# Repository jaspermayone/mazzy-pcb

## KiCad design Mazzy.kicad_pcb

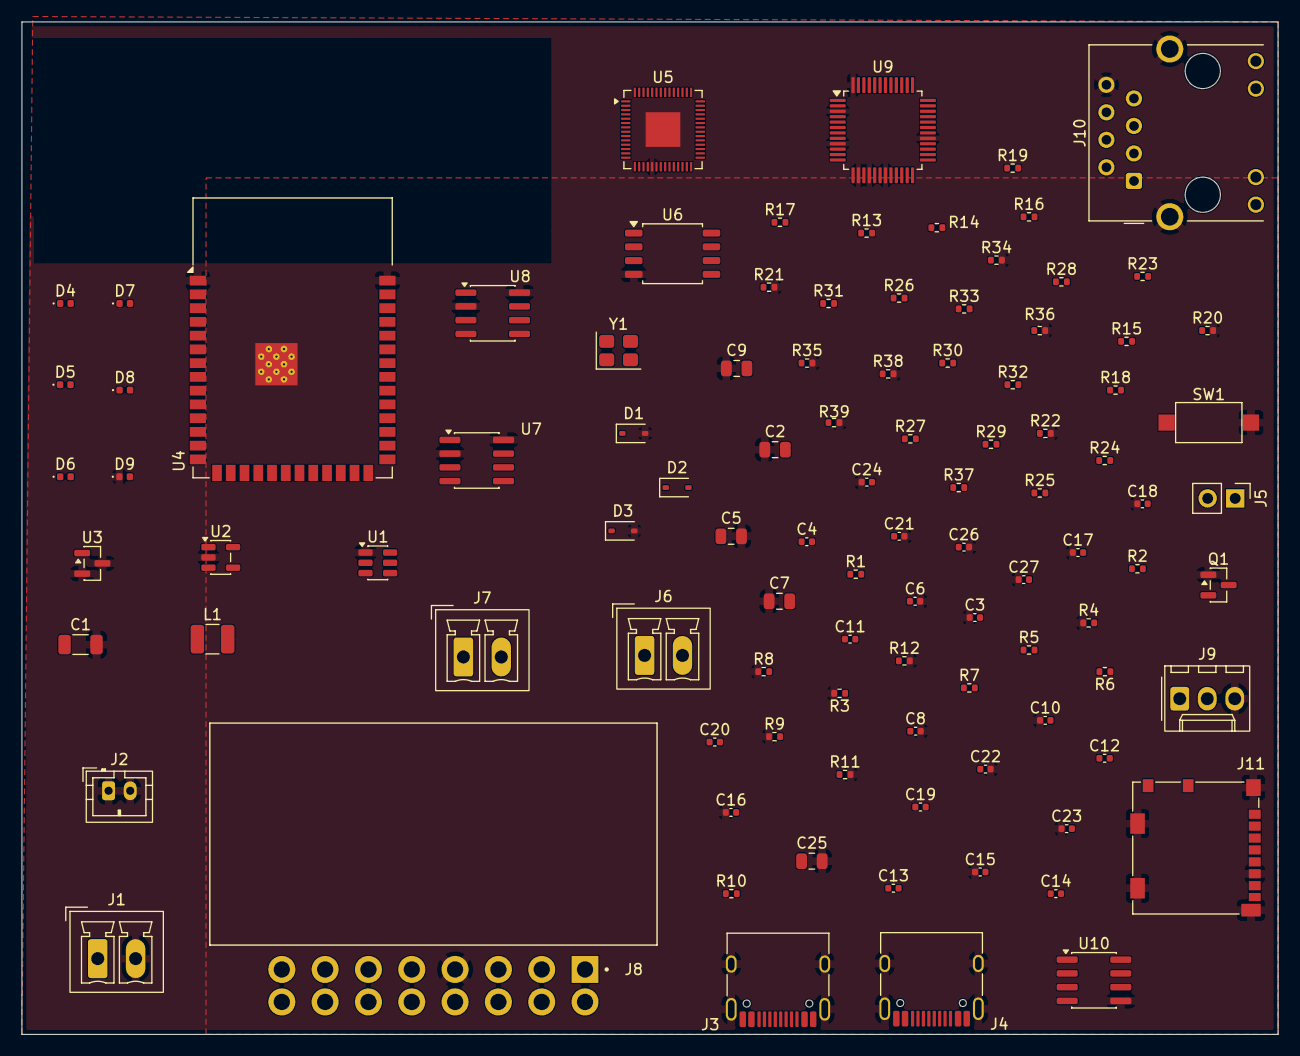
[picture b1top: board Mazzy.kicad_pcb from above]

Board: 2 copper layers, 116.0 x 93.5 mm, 100 parts (0 on the bottom side), 83 nets, no tracks yet.

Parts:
C1: 100uF; C_1206_3216Metric
C2, C9, C25: 10uF; C_0805_2012Metric
C3, C4, C6, C8, C10, C11, C12, C13, C14, C15, C16, C17, C18, C19, C20, C23, C24, C26, C27: 100nF; C_0402_1005Metric
C5: 22uF; C_0805_2012Metric
C7: 4.7uF; C_0805_2012Metric
C21, C22: 22pF; C_0402_1005Metric
D1: D_TVS; D_SOD-323
D2, D3: BAT54; D_SOD-323
D4, D5, D6, D7, D8, D9: LED; LED_0402_1005Metric
J1, J6, J7: Conn_01x02_Pin; PhoenixContact_MCV_1,5_2-G-3.5_1x02_P3.50mm_Vertical
J2: Conn_01x02_Pin; JST_PH_B2B-PH-K_1x02_P2.00mm_Vertical
J3, J4: USB_C_Receptacle_USB2.0_16P; USB_C_Receptacle_HRO_TYPE-C-31-M-12
J5: Conn_01x02_Pin; PinHeader_1x02_P2.54mm_Vertical
J8: OBD-II; COMTECH_C-OBD-II-16M
J9: SWC; Molex_KK-254_AE-6410-03A_1x03_P2.54mm_Vertical
J10: RJ45_Hanrun_HR911105A_Horizontal
J11: Micro_SD_Card_Det1; microSD_HC_Molex_104031-0811
L1: 10uH; L_1210_3225Metric
Q1: DMG2301L; SOT-23
R1, R2: 100k; R_0402_1005Metric
R3: 17.8k; R_0402_1005Metric
R4: 2k; R_0402_1005Metric
R5, R6, R7, R10, R26, R27, R28, R29, R30, R31, R32, R33: 10k; R_0402_1005Metric
R8, R9, R11, R12: 5.1k; R_0402_1005Metric
R13, R23: 49.9R; R_0402_1005Metric
R14, R15: 120R; R_0402_1005Metric
R16, R17, R18, R19, R21, R22: 330R; R_0402_1005Metric
R20: 12.4k; R_0402_1005Metric
R24, R25: 4.7k; R_0402_1005Metric
R34, R35, R36, R38, R39: 300R; R_0402_1005Metric
R37: 1k; R_0402_1005Metric
SW1: SW_Push; SW_SPST_CK_RS282G05A3
U1: TPS54302; SOT-23-6
U2: MCP73831-2-OT; SOT-23-5
U3: MCP100-300D; SOT-23
U4: ESP32-S3-WROOM-1
U5: RP2040; QFN-56-1EP_7x7mm_P0.4mm_EP3.2x3.2mm
U6: W25Q16JVSS; SOIC-8_5.3x5.3mm_P1.27mm
U7, U8: SN65HVD230; SOIC-8_3.9x4.9mm_P1.27mm
U9: W5500; LQFP-48_7x7mm_P0.5mm
U10: DS3231MZ; SOIC-8_3.9x4.9mm_P1.27mm
Y1: 25MHz; Crystal_SMD_3225-4Pin_3.2x2.5mm

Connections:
+3V3: C5.1, C6.1, C9.2, C10.2, C11.1, C12.1, C13.1, C14.1, C16.2, C17.2, C18.2, C19.1, C20.1, C26.1, D2.2 (A), J9.1, J10.9, J10.11, L1.2, R2.1, R5.2, R6.1, R7.1, R10.2, R13.1, R16.1, R17.1, R18.1, R19.1, R23.1, R24.1, R25.1, R26.1, R27.2, R28.1, R29.1, R30.2, R31.2, R32.1, R33.1, R37.1, U4.2 (3V3), U6.8 (VCC), U7.3 (VCC), U8.3 (VCC), U9.43 (PMODE2), U9.44 (PMODE1), U9.45 (PMODE0), U10.2 (VCC)
/CAN/HS_CANH: J6.1, J8.2, R14.2, U7.7 (CANH)
/CAN/HS_CANL: J6.2, J8.3, R14.1, U7.6 (CANL)
/CAN/MS_CANH: J7.1, R15.2, U8.7 (CANH)
/CAN/MS_CANL: J7.2, R15.1, U8.6 (CANL)
/Comms/<NO NET>: R17.2, U9.27 (ACTLED)
/Comms/RXN: J10.6 (RD-), U9.5 (RXN)
/Comms/RXP: J10.3 (RD+), U9.6 (RXP)
/Compute/BATT_LOW: U4.10 (IO17), U5.27 (GPIO16)
/Compute/CHRG_STAT: U4.9 (IO16), U5.28 (GPIO17)
/Compute/ESP_RX: U4.36 (RXD0), U5.2 (GPIO0)
/Compute/ESP_TX: U4.37 (TXD0), U5.3 (GPIO1)
/Compute/VBUS_RP: J4.A4 (VBUS), J4.A9 (VBUS), J4.B4 (VBUS), J4.B9 (VBUS)
/Peripherals/SD_DET: J11.9 (DET), R29.2
/Power/12V_PROTECTED: C1.1, C2.2, C3.2, D1.1 (A1), Q1.2 (S), R1.1, U1.3 (VIN), U2.4 (V_{DD})
/Power/12V_RAW: J1.1, Q1.3 (D)
/Power/BATT_LOW: R6.2, U3.1 (~RST)
/Power/PWR_SYS: D2.1 (K), D3.1 (K)
GND: C1.2, C2.1, C3.1, C5.2, C6.2, C7.1, C8.2, C9.1, C10.1, C15.1, C16.1, C17.1, C18.1, C21.2, C22.2, C23.1, C24.1, C25.2, C26.2, C27.1, D1.2 (A2), D3.2 (A), D9.1 (K), J1.2, J2.1, J2.2, J3.A1 (GND), J3.A12 (GND), J3.B1 (GND), J3.B12 (GND), J3.SH (SHIELD), J4.A1 (GND), J4.A12 (GND), J4.B1 (GND), J4.B12 (GND), J4.SH (SHIELD), J8.4, J9.3, J10.8, J10.SH, J11.6 (VSS), J11.SH (SHIELD), Q1.1 (G), R3.2, R4.1, R8.1, R9.1, R11.2, R12.2, R20.2, R21.2, R22.2, R34.2, R35.2, R36.2, R38.2, R39.2, SW1.2, U1.1 (GND), U2.2 (V_{SS}), U3.2 (VDD), U3.3 (VSS), U4.1 (GND), U4.40 (GND), U4.41 (GND), U5.19 (TESTEN), U5.57 (GND), U6.4 (GND), U7.2 (GND), U7.8 (Rs), U8.2 (GND), U8.8 (Rs), U9.3 (AGND), U9.9 (AGND), U9.14 (AGND), U9.16 (AGND), U9.19 (AGND), U9.29 (GND), U9.48 (AGND), U10.5 (GND)
unnamed: C13.2, U5.1 (IOVDD), U5.10 (IOVDD), U5.22 (IOVDD), U5.33 (IOVDD), U5.42 (IOVDD), U5.49 (IOVDD)
unnamed: C20.2, U9.4 (AVDD), U9.8 (AVDD), U9.11 (AVDD), U9.15 (AVDD), U9.17 (AVDD), U9.21 (AVDD)
unnamed: D4.1 (K), R34.1
unnamed: D5.1 (K), R35.1
unnamed: D6.1 (K), R36.1
unnamed: D7.1 (K), R38.1
unnamed: D8.1 (K), R39.1
unnamed: D9.2 (A), R37.2
unnamed: J3.A5 (CC1), R9.2
unnamed: J3.B5 (CC2), R8.2
unnamed: J4.A5 (CC1), R12.1
unnamed: J4.B5 (CC2), R11.1
unnamed: J5.1, U5.24 (SWCLK)
unnamed: J5.2, U5.25 (SWDIO)
unnamed: J10.10, R22.1
unnamed: J10.12, R21.1
unnamed: J10.5 (RCT), R23.2
unnamed: J10.4 (TCT), R13.2
unnamed: J10.1 (TD+), U9.2 (TXP)
unnamed: J10.2 (TD-), U9.1 (TXN)
unnamed: J11.5 (CLK), R31.1
unnamed: J11.3 (CMD), R32.2
unnamed: J11.7 (DAT0), R30.1
unnamed: J11.8 (DAT1), R28.2
unnamed: J11.1 (DAT2), R27.1
unnamed: J11.2 (DAT3/CD), R33.2
unnamed: C27.2, J11.4 (VDD)
unnamed: C4.2, U1.6 (BOOT)
unnamed: R1.2, U1.5 (EN)
unnamed: R2.2, R3.1, U1.4 (FB)
unnamed: C4.1, L1.1, U1.2 (SW)
unnamed: R4.2, U2.5 (PROG)
unnamed: R5.1, U2.1 (STAT)
unnamed: C7.2, U2.3 (V_{BAT})
unnamed: C8.1, R7.2, U4.3 (EN)
unnamed: J3.A6 (D+), J3.B6 (D+), U4.14 (USB_D+)
unnamed: J3.A7 (D-), J3.B7 (D-), U4.13 (USB_D-)
unnamed: C12.2, U5.43 (ADC_AVDD)
unnamed: U5.52 (QSPI_SCLK), U6.6 (CLK)
unnamed: U5.53 (QSPI_SD0), U6.5 (DI/IO_{0})
unnamed: U5.55 (QSPI_SD1), U6.2 (DO/IO_{1})
unnamed: U5.54 (QSPI_SD2), U6.3 (~WP/IO_{2})
unnamed: U5.51 (QSPI_SD3), U6.7 (~HOLD/~RESET/IO_{3})
unnamed: R10.1, SW1.1, U5.26 (RUN)
unnamed: J4.A7 (D-), J4.B7 (D-), U5.46 (USB_DM)
unnamed: J4.A6 (D+), J4.B6 (D+), U5.47 (USB_DP)
unnamed: C11.2, U5.48 (USB_VDD)
unnamed: C14.2, U5.44 (VREG_VIN)
unnamed: C15.2, U5.23 (DVDD), U5.45 (VREG_VOUT), U5.50 (DVDD)
unnamed: U5.56 (~QSPI_SS), U6.1 (~CS)
unnamed: C25.1, U9.22 (1V2O)
unnamed: R16.2, U9.26 (DUPLED)
unnamed: R20.1, U9.10 (EXRES1)
unnamed: R19.2, U9.25 (LINKLED)
unnamed: R18.2, U9.24 (SPDLED)
unnamed: C24.2, U9.20 (TOCAP)
unnamed: C23.2, U9.18 (VBG)
unnamed: C19.2, U9.28 (VDD)
unnamed: C22.1, U9.30 (XI/CLKIN), Y1.2
unnamed: C21.1, U9.31 (XO), Y1.1
unnamed: R24.2, U10.8 (SCL)
unnamed: R25.2, U10.7 (SDA)
unnamed: R26.2, U10.3 (~INT/SQW)
VBUS: J3.A4 (VBUS), J3.A9 (VBUS), J3.B4 (VBUS), J3.B9 (VBUS)

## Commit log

2026-04-27 whip;2;13~
2026-04-27 add gitignore
2026-04-27 add .gitattributes
2026-04-27 Stop tracking KiCad .history local history directory
2026-04-27 Stop tracking KiCad local project settings file
